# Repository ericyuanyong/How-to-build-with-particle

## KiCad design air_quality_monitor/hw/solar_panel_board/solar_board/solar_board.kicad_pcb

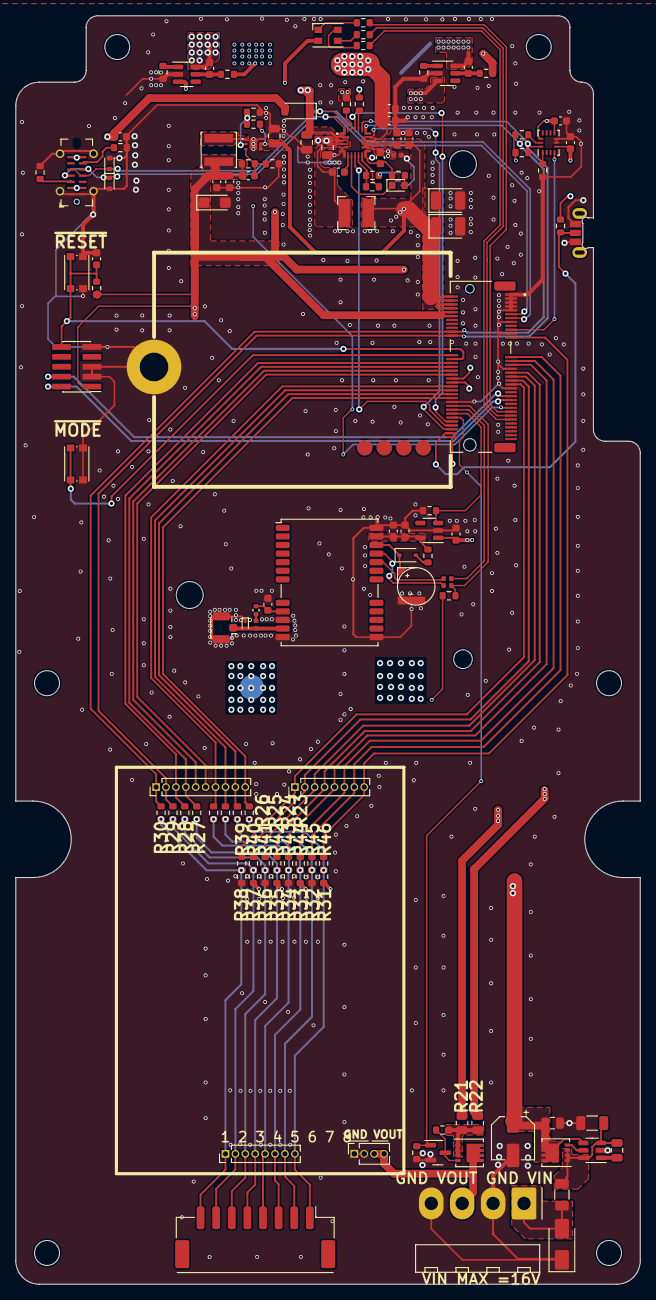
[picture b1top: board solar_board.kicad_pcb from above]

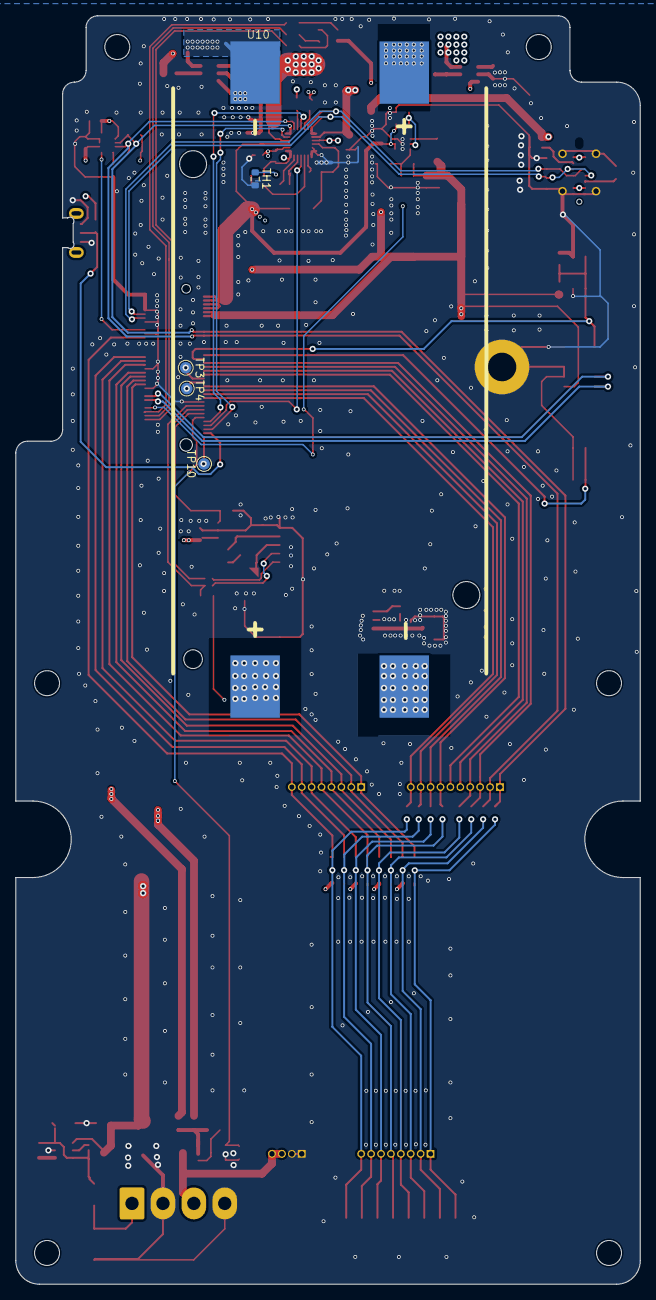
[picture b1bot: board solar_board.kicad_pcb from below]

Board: 4 copper layers, 80.0 x 162.5 mm, 135 parts (5 on the bottom side), 95 nets.

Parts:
@HOLE4, @HOLE5, @HOLE6, @HOLE7, @HOLE8, @HOLE9: (no value)
C1: 2.2uF; C_1206_3216Metric
C2, C10: 10uF; C_0805_2012Metric
C3: 4.7uF; C_0805_2012Metric
C4: 47uF; CP_Elec_5x5.8
C5, C6: 1uF; C_0805_2012Metric
C7: 47nF; C_0603_1608Metric
C8, C24: 10uF; C_0603_1608Metric
C9, C11, C12: 22pF; C_0603_1608Metric
C13, C17, C19, C26: 22uF; C_0603_1608Metric
C14, C15, C16, C18, C20, C21, C23, C25, C27: 0.1uF; C_0603_1608Metric
C22: Super cap; SM3R370301U
C28, C29: 220uF; CP_EIA-3528-12_Kemet-T
C30: 220uF; CP_EIA-3216-10_Kemet-I
D1: LED; LED_0603_1608Metric
D2: LED_RAGB; LED_Cree-PLCC4_3.2x2.8mm_CCW
D3, D4: ESD5Zxx; D_SOD-523
D5: SMAJ28CA; D_SMA
D6: D; D_SOD-323
D7: ESD9B3.3ST5G; D_SOD-923
D8: 1N4448W; D_SOD-123
F1: Fuse; Fuse_1206_3216Metric
FB1, FB2, FB3: L_0402_1005Metric
J1, J8: Conn_01x08; PinHeader_1x08_P1.27mm_Vertical
J2: USB_C_Receptacle_USB2.0_16P; USB_C_Receptacle_G-Switch_GT-USB-7051x
J3: Conn_01x08_Pin; Molex_CLIK-Mate_502443-0870_1x08-1MP_P2.00mm_Vertical
J4: Conn_01x04_Pin; Molex_KK-396_A-41792-0004_1x04_P3.96mm_Horizontal
J5: Conn_Coaxial; U.FL_Hirose_U.FL-R-SMT-1_Vertical
J6: Conn_ARM_JTAG_SWD_10; PinHeader_2x05_P1.27mm_Vertical_SMD
J7: Conn_01x10; PinHeader_1x10_P1.27mm_Vertical
J9: Conn_01x04_Pin; PinSocket_1x04_P1.27mm_Vertical
L1: 2.2uH; L_Changjiang_FNR4020S
L2: 1uH; L_Bourns-SRN4018
L3: 10nH; L_0402_1005Metric
Q1: DMN3008SFG; Diodes_PowerDI3333-8
Q2: DMP3013SFV; Diodes_PowerDI3333-8
Q3: BSS138; SOT-23
R1, R4, R5, R19, R20: 100K; R_0603_1608Metric
R2: DNP; R_0603_1608Metric
R3, R6, R7, R8, R9: TBD; R_0603_1608Metric
R10, R11, R14, R15, R16: 1K; R_0603_1608Metric
R12, R13: 100R; R_0603_1608Metric
R17, R18: 5.1K; R_0603_1608Metric
R21: DNP; R_0805_2012Metric
R22: 0R; R_0805_2012Metric
R23, R24, R25, R26, R27, R28, R29, R30, R31, R32, R33, R34, R35, R36, R37, R38, R39, R40, R41, R42, R43, R44, R45, R46, R47: 0R; R_0603_1608Metric
R48, R49: 470; R_0603_1608Metric
R50, R51: 4.7K; R_0603_1608Metric
R52, R53, R54: 10K; R_0603_1608Metric
R55: 470; R_0402_1005Metric
SW1: ~{MODE}; SW_Push_1P1T_NO_CK_KMR2
SW2: ~{RESET}; SW_Push_1P1T_NO_CK_KMR2
TH1: NTC; R_0603_1608Metric
TP3, TP4, TP10: TestPoint_Pad_D1.5mm
U1: MSoM; Particle_MSOM
U2: MP2733; QFN-26
U3: LM74700; SOT-23-6
U4: TPS62291DRVR; WSON-6-EP
U5, U6: DW06D; SOT-23-6
U7: LDLN025M18R; SOT-23-5
U8: NEO-M8U; ublox_NEO
U9: BMI160; Bosch_LGA-14_3x2.5mm_P0.5mm
U10: KEYSTONE_1134
U11: PTS847MM350LSMTR2LFS

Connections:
+3.3V: C9.1, C11.1, C12.1, C20.1, C21.1, C30.1, D2.2 (A), J6.1 (VTref), L1.2, R4.1, R31.2, R33.2, R35.2, R37.2, R50.2, R51.2, R52.2, R53.2, R54.2, U1.10 (3.3V), U1.12 (3.3V), U9.5 (VDDIO), U9.8 (VDD), U9.12 (CSB)
/power management/VREF: C8.1, R7.2, R8.2, U2.13 (VREF), U2.14 (VREF)
ACCEL_INT: U1.19 (D20), U9.4 (INT1)
D+: D4.1 (K), J2.A6 (D+), J2.B6 (D+), U1.11 (USB_P), U2.1 (USB_DP), U2.26 (USB_DP)
D-: D3.1 (K), J2.A7 (D-), J2.B7 (D-), U1.13 (USB_N), U2.25 (USB_DM)
DCDC_MODE: R1.2, R2.1, U1.59 (D26), U4.2 (MODE)
EXT_A0: J8.8, R46.2, U1.23 (ADC0)
EXT_A1: J8.7, R45.2, U1.33 (ADC1)
EXT_A2: J8.6, R44.2, U1.35 (ADC2)
EXT_A3: J8.5, R43.2, U1.37 (ADC3)
EXT_A4: J8.4, R42.2, U1.41 (ADC4)
EXT_A5: J8.3, R41.2, U1.43 (ADC5)
EXT_A6: J8.2, R40.2, U1.45 (ADC6)
EXT_A7: J8.1, R39.2, U1.47 (ADC7)
EXT_I2C_SCL: J7.1, R30.2, R50.1, U1.20 (SCL), U2.19 (SCL), U2.20 (SCL), U9.13 (SCx)
EXT_I2C_SDA: J7.2, R29.2, R51.1, U1.22 (SDA), U2.21 (SDA), U9.14 (SDx)
EXT_SPI_CS: J7.7, R26.2, U1.48 (CS)
EXT_SPI_MISO: J7.8, R25.2, U1.50 (MISO)
EXT_SPI_MOSI: J7.9, R24.2, U1.52 (MOSI)
EXT_SPI_SCLK: J7.10, R23.2, U1.54 (SCLK)
EXT_UART_CTS: J7.5, U1.40 (CTS)
EXT_UART_RTS: J7.6, U1.42 (RTS)
EXT_UART_RXD: J7.4, R27.2, U1.38 (RXD)
EXT_UART_TXD: J7.3, R28.2, U1.36 (TXD)
GND: C1.2, C3.2, C4.2, C5.2, C6.2, C10.2, C11.2, C12.2, C13.2, C14.2, C17.2, C18.2, C19.2, C20.2, C21.2, C22.2, C23.2, C24.2, C25.2, C26.2, C27.2, C28.2, C29.2, C30.2, D3.2 (A), D4.2 (A), D5.1 (A1), D7.1 (A1), FB3.2, J2.A1 (GND), J2.A12 (GND), J2.B1 (GND), J2.B12 (GND), J2.S1 (SHIELD), J4.2, J4.4, J5.2 (Ext), J6.3 (GND), J6.5 (GND), J6.9 (GNDDetect), J9.1, J9.2, Q3.2 (S), R2.2, R5.2, R10.1, R11.1, R17.1, R18.1, R20.2, R32.2, R34.2, R36.2, R38.2, R47.1, R48.1, SW1.2, SW2.2, TH1.2, U1.1 (GND), U1.3 (GND), U1.5 (GND), U1.7 (GND), U1.9 (GND), U1.15 (GND), U1.21 (GND), U1.39 (GND), U1.49 (GND), U1.56 (GND), U1.80 (GND), U2.5 (PGND), U2.6 (PGND), U2.7 (PGND), U3.2 (GND), U4.6 (GND), U4.7 (PAD), U5.2 (S1), U6.2 (S1), U7.2 (GND), U8.10 (GND), U8.12 (GND), U8.13 (GND), U8.24 (GND), U9.6 (GNDIO), U9.7 (GND), U11.1, U11.3
GNDA: C8.2, FB3.1, R3.2, U2.15 (AGND)
GNSS_PWR_EN: R47.2, U1.62 (D22), U7.3 (EN)
GNSS_RXD: FB2.1, R53.1, U1.58 (D24)
GNSS_TXD: FB1.1, U1.60 (D25)
NEGATIVE_1: C16.1, U6.3 (S2), U6.6 (VSS), U10.2 (NEGATIVE_1)
NEGATIVE_2: C15.1, U5.3 (S2), U5.6 (VSS), U10.4 (NEGATIVE_2)
unnamed: D1.2 (A), R7.1
unnamed: D1.1 (K), U2.9 (STAT)
unnamed: D2.4 (BK), R16.1
unnamed: D2.3 (GK), R15.1
unnamed: D2.1 (RK), R14.1
unnamed: D6.2 (A), R49.1
unnamed: C22.1, D6.1 (K), U8.22 (V_BCKP)
unnamed: D7.2 (A2), J5.1 (In), L3.1, U8.11 (RF_IN)
unnamed: C3.1, C4.1, C5.1, D8.1 (K), Q1.5 (D), U2.2 (VIN), U3.4 (CATHODE)
unnamed: J1.1, J3.8, R30.1, R38.1, R39.1
unnamed: J1.2, J3.7, R29.1, R37.1, R40.1
unnamed: J1.3, J3.6, R28.1, R36.1, R41.1
unnamed: J1.4, J3.5, R27.1, R35.1, R42.1
unnamed: J1.5, J3.4, R26.1, R34.1, R43.1
unnamed: J1.6, J3.3, R25.1, R33.1, R44.1
unnamed: J1.7, J3.2, R24.1, R32.1, R45.1
unnamed: J1.8, J3.1, R23.1, R31.1, R46.1
unnamed: J2.A5 (CC1), R18.2
unnamed: J2.B5 (CC2), R17.2
unnamed: J6.4 (SWCLK/TCK), U1.53 (SWD_CLK)
unnamed: J6.2 (SWDIO/TMS), U1.55 (SWD_DIO)
unnamed: L3.2, R55.1
unnamed: Q1.4 (G), U3.5 (GATE)
unnamed: Q2.4 (G), Q3.3 (D), R19.2
unnamed: Q2.1 (S), Q2.2 (S), Q2.3 (S), R19.1, R21.1, R22.1
unnamed: R9.2, TH1.1
unnamed: SW1.1, U1.32 (~MODE)
unnamed: R54.1, U1.72 (D7), U11.2
unnamed: TP4.1, U1.46 (MODEM_USB_N)
unnamed: TP3.1, U1.44 (MODEM_USB_P)
unnamed: TP10.1, U1.74 (MODEM_VBUS)
unnamed: R16.2, U1.65 (RGB_BLUE)
unnamed: R15.2, U1.63 (RGB_GREEN)
unnamed: R14.2, U1.61 (RGB_RED)
unnamed: C7.1, U2.8 (BST)
unnamed: R8.1, U2.22 (DISC)
unnamed: R3.1, U2.24 (ILIM)
unnamed: R6.1, R9.1, U2.11 (NTC)
unnamed: C7.2, L2.1, U2.4 (SW)
unnamed: R6.2, U2.12 (VNTC)
unnamed: C1.1, C2.1, F1.2, Q1.1 (S), Q1.2 (S), Q1.3 (S), U3.3 (EN), U3.6 (ANODE)
unnamed: C2.2, U3.1 (VCAP)
unnamed: C9.2, R4.2, R5.1, U4.3 (FB)
unnamed: L1.1, U4.1 (SW)
unnamed: R10.2, U5.1 (V-)
unnamed: C15.2, R12.1, U5.5 (VDD)
unnamed: R11.2, U6.1 (V-)
unnamed: C16.2, R13.1, U6.5 (VDD)
unnamed: C18.1, C19.1, R49.2, U7.5 (OUT), U8.23 (VCC)
unnamed: FB2.2, U8.21 (RXD/SPI_MOSI)
unnamed: FB1.2, U8.20 (TXD/SPI_MISO)
unnamed: C23.1, R55.2, U8.9 (VCC_RF)
unnamed: R48.2, U9.1 (SDO)
PMIC_INT: U1.68 (D5), U2.10 (INT)
PMIC_OTG: U1.66 (D4), U2.23 (OTG)
PMID: C10.1, R21.2, U2.3 (PMID)
POSITIVE_1: C26.1, C27.1, R12.2, R13.2, U2.17 (BATT), U10.1 (POSITIVE_1), U10.3 (POSITIVE_2)
PWR_IN: D5.2 (A2), F1.1, J4.1
PWR_OUT: J4.3, J9.3, J9.4, Q2.5 (D)
PWR_VOUT_CTL: Q3.1 (G), R20.1, U1.64 (D23)
VSYS: C6.1, C13.1, C14.1, C17.1, C28.1, C29.1, L2.2, R1.1, R22.2, U1.2 (VCC), U1.4 (VCC), U1.6 (VCC), U1.8 (VCC), U2.16 (SYS), U4.4 (EN), U4.5 (VIN), U7.1 (IN)
VUSB: C24.1, D8.2 (A), J2.A4 (VBUS), J2.A9 (VBUS), J2.B4 (VBUS), J2.B9 (VBUS)
~PMIC_CE: U1.70 (D6), U2.18 (~CE)
~RESET: C25.1, J6.10 (~RESET), R52.1, SW2.1, U1.34 (~RESET)

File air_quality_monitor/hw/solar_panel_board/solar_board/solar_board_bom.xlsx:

Ref | Qnty | Value | Cmp name | Footprint | PN | Purchased QTY
C1 | 1 | 22nF | C_Small | Capacitor_SMD:C_1206_3216Metric |  | 5
C2, C3 | 2 | 0.1uF | C_Small | Capacitor_SMD:C_0805_2012Metric |  | 10
C4 | 1 | 47uF | C_Polarized_US | Capacitor_SMD:CP_Elec_5x5.8 |  | 5
C5 | 1 | 4.7uF | C_Small | Capacitor_SMD:C_0805_2012Metric |  | 5
C6, C10 | 2 | 10uF | C_Small | Capacitor_SMD:C_0805_2012Metric |  | 10
C7 | 1 | 47nF | C_Small | Capacitor_SMD:C_0603_1608Metric |  | 5
C8, C11, C24 | 3 | 10uF | C | Capacitor_SMD:C_0603_1608Metric |  | 15
C9 | 1 | NC | C_Small | Capacitor_SMD:C_0603_1608Metric |  | 5
C12, C14, C15, C16, C18, C20, C21, C23, C25, C27 | 10 | 0.1uF | C_Small | Capacitor_SMD:C_0603_1608Metric |  | 50
C13, C17, C19, C26 | 4 | 22uF | C_Small | Capacitor_SMD:C_0603_1608Metric |  | 20
C22 | 1 | 0.07F | C_Polarized_US | particle_kicad_lib:SM3R370301U |  | 5
C28, C29 | 2 | 220uF | C | Capacitor_Tantalum_SMD:CP_EIA-3528-12_Kemet-T |  | 10
C30 | 1 | 220uF | C | Capacitor_Tantalum_SMD:CP_EIA-3216-10_Kemet-I |  | 5
D1 | 1 | LED | LED | LED_SMD:LED_0603_1608Metric |  | 5
D2 | 1 | LED_RAGB | LED_RAGB | LED_SMD:LED_Cree-PLCC4_3.2x2.8mm_CCW |  | 5
D3, D4 | 2 | ESD5Zxx | ESD5Zxx | Diode_SMD:D_SOD-523 |  | 10
D5 | 1 | SMAJ20CA | SMAJ28CA | Diode_SMD:D_SMA |  | 5
D6 | 1 | 1A/0.4V | D | Diode_SMD:D_SOD-323 |  | 5
D7 | 1 | ESD9B3.3ST5G | ESD9B3.3ST5G | Diode_SMD:D_SOD-923 |  | 5
D8 | 1 | 1N4448W | 1N4448W | Diode_SMD:D_SOD-123 |  | 5
F1 | 1 | 40V/2A | Fuse | Fuse:Fuse_1206_3216Metric |  | 5
FB1, FB2, FB3 | 3 | ~ | FerriteBead_Small | Inductor_SMD:L_0402_1005Metric |  | 15
J1, J8 | 2 | Conn_01x08 | Conn_01x08 | Connector_PinHeader_1.27mm:PinHeader_1x08_P1.27mm_Vertical |  | 10
J2 | 1 | USB_C_Receptacle_USB2.0_16P | USB_C_Receptacle_USB2.0_16P | Connector_USB:USB_C_Receptacle_G-Switch_GT-USB-7051x |  | 5
J3 | 1 | Conn_01x08_Pin | Conn_01x08_Pin | Connector_Molex:Molex_CLIK-Mate_502443-0870_1x08-1MP_P2.00mm_Vertical |  | 5
J4 | 1 | Conn_01x04_Pin | Conn_01x04_Pin | Connector_Molex:Molex_KK-396_A-41792-0004_1x04_P3.96mm_Horizontal |  | 5
J5 | 1 | Conn_Coaxial | Conn_Coaxial | Connector_Coaxial:U.FL_Hirose_U.FL-R-SMT-1_Vertical |  | 5
J6 | 1 | Conn_ARM_JTAG_SWD_10 | Conn_ARM_JTAG_SWD_10 | Connector_PinHeader_1.27mm:PinHeader_2x05_P1.27mm_Vertical_SMD |  | 5
J7 | 1 | Conn_01x10 | Conn_01x10 | Connector_PinHeader_1.27mm:PinHeader_1x10_P1.27mm_Vertical |  | 5
J9 | 1 | Conn_01x04_Pin | Conn_01x04_Pin | Connector_PinSocket_1.27mm:PinSocket_1x04_P1.27mm_Vertical |  | 5
L1 | 1 | 2.2uH | L | Inductor_SMD:L_Changjiang_FNR4020S |  | 5
L2 | 1 | 1uH | L | Inductor_SMD:L_Bourns-SRN4018 |  | 5
L3 | 1 | 10nH | L | Inductor_SMD:L_0402_1005Metric |  | 5
Q1 | 1 | DMN3008SFG | DMN3008SFG | Package_SON:Diodes_PowerDI3333-8 |  | 5
Q2 | 1 | DMP3013SFV | DMP3013SFV | Package_SON:Diodes_PowerDI3333-8 |  | 5
Q3 | 1 | BSS138 | BSS138 | Package_TO_SOT_SMD:SOT-23 |  | 5
R1, R19, R20, R47, R48 | 5 | 100K | R_US | Resistor_SMD:R_0603_1608Metric |  | 25
R2 | 1 | DNP | R_Small | Resistor_SMD:R_0603_1608Metric |  | 5
R3 | 1 | 60R | R_Small | Resistor_SMD:R_0603_1608Metric |  | 5
R4, R23, R24, R25, R26, R27, R28, R29, R30, R31, R32, R33, R34, R35, R36, R37, 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 | 25 | 0R | R_US | Resistor_SMD:R_0603_1608Metric |  | 125
R5 | 1 | NC | R_Small | Resistor_SMD:R_0603_1608Metric |  | 5
R6 | 1 | 11.8K | R_Small | Resistor_SMD:R_0603_1608Metric |  | 5
R7, R8, R52, R53, R54 | 5 | 10K | R_Small | Resistor_SMD:R_0603_1608Metric |  | 25
R9 | 1 | 3.06K | R_Small | Resistor_SMD:R_0603_1608Metric |  | 5
R10, R11, R14, R15, R16 | 5 | 1K | R_Small | Resistor_SMD:R_0603_1608Metric |  | 25
R12, R13, R49 | 3 | 100R | R_US | Resistor_SMD:R_0603_1608Metric |  | 15
R17, R18 | 2 | 5.1K | R_Small | Resistor_SMD:R_0603_1608Metric |  | 10
R21 | 1 | DNP | R_US | Resistor_SMD:R_0805_2012Metric |  | 5
R22 | 1 | 0R | R_US | Resistor_SMD:R_0805_2012Metric |  | 5
R50, R51 | 2 | 4.7K | R_Small | Resistor_SMD:R_0603_1608Metric |  | 10
R55 | 1 | 10R | R_US | Resistor_SMD:R_0402_1005Metric |  | 5
SW1 | 1 | ~{MODE} | SW_MEC_5E | Button_Switch_SMD:SW_Push_1P1T_NO_CK_KMR2 |  | 5
SW2 | 1 | ~{RESET} | SW_MEC_5E | Button_Switch_SMD:SW_Push_1P1T_NO_CK_KMR2 |  | 5
TH1 | 1 | 103AT | Thermistor_NTC | Resistor_SMD:R_0603_1608Metric |  | 5
TP3, TP4, TP10 | 3 | ~ | TestPoint | TestPoint:TestPoint_Pad_D1.5mm |  | 15
U1 | 1 | MSoM | Particle_MSoM | particle_kicad_lib:Particle_MSOM |  | 5
U2 | 1 | MP2733 | MP2733 | particle_kicad_lib:QFN-26 |  | 5
U3 | 1 | LM74700 | LM74700 | Package_TO_SOT_SMD:SOT-23-6 |  | 5
U4 | 1 | TPS62291DRVR | TPS62291DRVR | particle_kicad_lib:WSON-6-EP |  | 5
U5, U6 | 2 | DW06D | DW06D | Package_TO_SOT_SMD:SOT-23-6 |  | 10
U7 | 1 | LDLN025M18R | LDLN025M18R | Package_TO_SOT_SMD:SOT-23-5 |  | 5
U8 | 1 | NEO-M8U | NEO-M8N | RF_GPS:ublox_NEO |  | 5
U9 | 1 | BMI160 | BMI160 | Package_LGA:Bosch_LGA-14_3x2.5mm_P0.5mm |  | 5
U10 | 1 | ~ | LIPO_18650 | particle_kicad_lib:KEYSTONE_1134 |  | 5
U11 | 1 | ~ | TACTEL_SWITCH | particle_kicad_lib:PTS847MM350LSMTR2LFS |  | 5

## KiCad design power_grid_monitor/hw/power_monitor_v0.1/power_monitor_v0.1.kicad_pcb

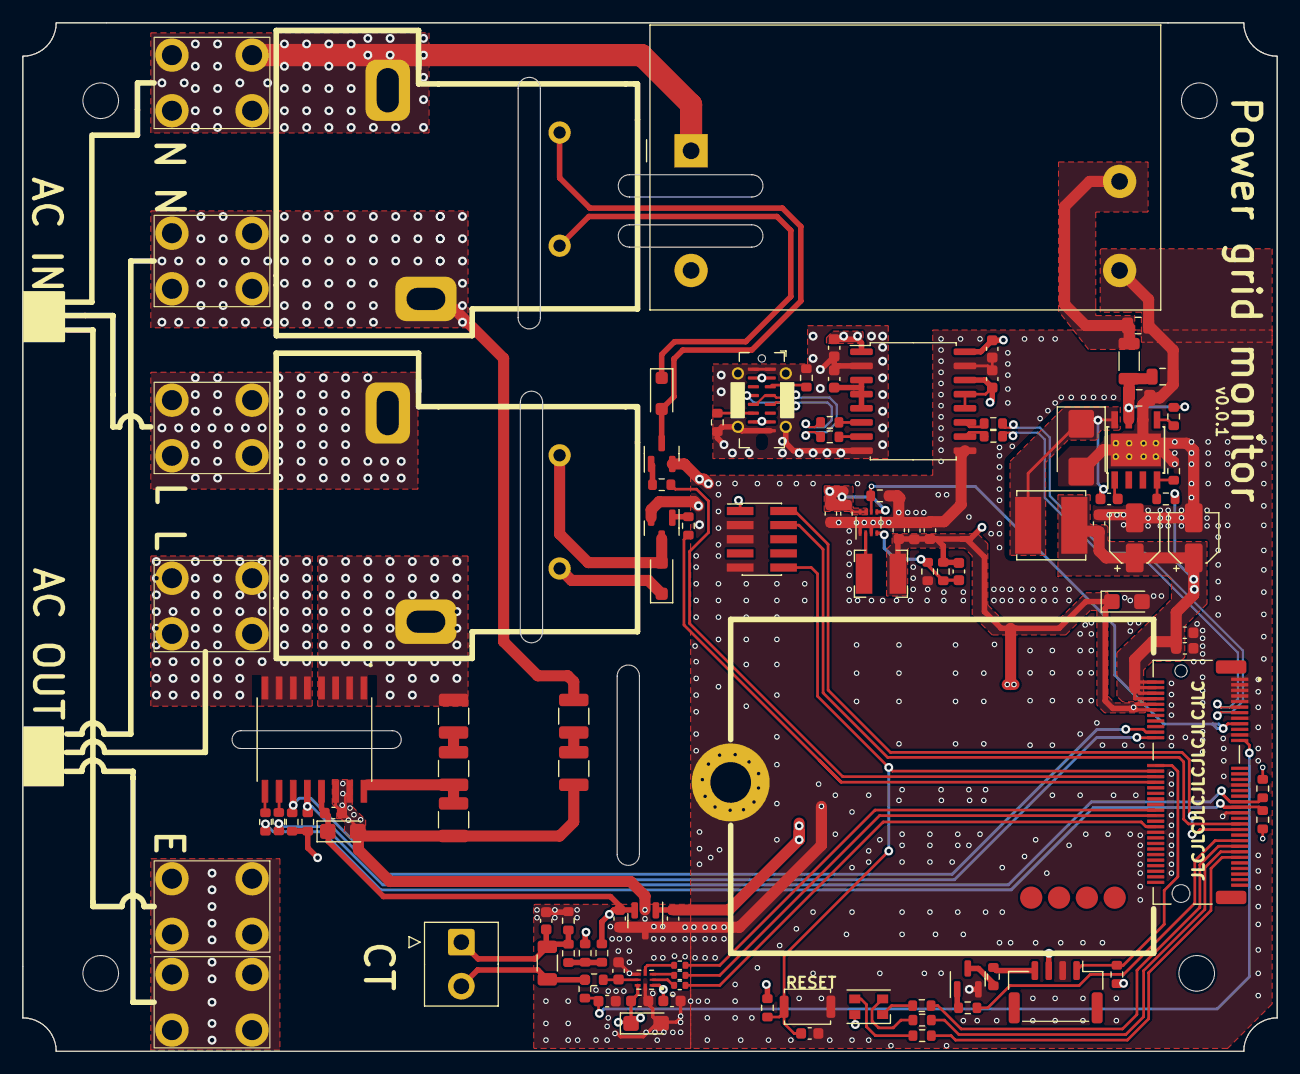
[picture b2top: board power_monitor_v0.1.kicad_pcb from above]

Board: 4 copper layers, 112.7 x 92.4 mm, 105 parts (0 on the bottom side), 72 nets.

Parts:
C1, C2: 0.1uF; C_0805_2012Metric
C3: 22uF; C_0805_2012Metric
C4: 10nF; C_0603_1608Metric
C5, C6: 330uF; CP_Elec_4x5.3
C7, C13, C14, C17, C18, C19, C21, C24, C25, C27, C28, C29, C30: 0.1uF; C_0603_1608Metric
C8: 0.47uF; C_0603_1608Metric
C9: 1uF; C_0603_1608Metric
C10: 8.2pF; C_0603_1608Metric
C11, C12, C15, C26: 10uF; C_0603_1608Metric
C16, C20: 47uF; CP_EIA-3216-12_Kemet-S
C22: 10pF; C_0603_1608Metric
C23: 47uF; CP_EIA-3216-10_Kemet-I
C31: NC; C_0603_1608Metric
D1: B360; D_SMB
D2, D3: 1N4148WS; D_SOD-123F
D4: LED_RAGB; LED_Cree-PLCC4_3.2x2.8mm_CCW
FB1: FerriteBead; L_1206_3216Metric
J1: TE_826576-2_1x02_P3.96mm_Vertical
J2: AC_LIVE_IN; T34001
J3: AC_NEUTRAL_IN; T34001
J4: AC_EARTH_IN; T34001
J5: AC_NEUTRAL_OUT; T34001
J6: AC_LIVE_OUT; T34001
J7: AC_EARTH_OUT; T34001
J8: USB_C_Receptacle_USB2.0_16P; USB_C_Receptacle_G-Switch_GT-USB-7051x
J9: Conn_ARM_JTAG_SWD_10; PinHeader_2x05_P1.27mm_Vertical_SMD
J10: button with LED; JST_GH_BM04B-GHS-TBT_1x04-1MP_P1.25mm_Vertical
K1, K2: Relay_SPST-NO; T9VV1K15-12S
L1: 10uH; L_Bourns_SRN6045TA
L2: 10uH; L_Bourns-SRN4018
PS1: IRM-10-12; Converter_ACDC_MeanWell_IRM-10-xx_THT
Q1, Q2, Q3: BSS138; SOT-23
R1, R14, R40, R41: NC; R_0603_1608Metric
R2: 10K 1%; R_0603_1608Metric
R3: 4.42K 1%; R_0603_1608Metric
R4: 820K 1%; R_0603_1608Metric
R5: 182K 1%; R_0603_1608Metric
R6, R12, R13: 100K; R_0603_1608Metric
R7, R32, R42: 10K; R_0603_1608Metric
R8, R9, R10: 22R; R_0402_1005Metric
R11: 51R; R_1206_3216Metric
R15, R36, R37: 0R; R_0603_1608Metric
R16: 10R; R_0603_1608Metric
R17, R18, R20, R21: 1M; R_1210_3225Metric
R19: TBD; R_1210_3225Metric
R22, R23, R25, R26, R27, R38, R39: 1K; R_0603_1608Metric
R24, R28, R31, R33: 22R; R_0603_1608Metric
R29, R30: 4.7K; R_0603_1608Metric
R34, R35: 5.1K; R_0603_1608Metric
RESET1: SW_Push; SW_Push_SPST_NO_Alps_SKRK
U1: ACS37800; SOIC127P1030X265-16N
U2: ADS7042xDCU; QFN50P150X150X40-8N
U3: REF3033; SOT-23
U4: TPS5430DDA; TI_SO-PowerPAD-8_ThermalVias
U5: TPS62065; WSON-8-1EP_2x2mm_P0.5mm_EP0.9x1.6mm
U6: MSoM; Particle_MSOM
U7: ADUM4160; SOIC-16W_7.5x10.3mm_P1.27mm
U8: ENCLOSURE

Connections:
+3.3VA: C9.2, C16.1, C17.2, C19.2, C20.1, C30.2, R15.1, U1.13 (VCC), U2.1 (DVDD), U2.7 (AVDD), U3.2 (OUT)
+3V3: C10.2, C11.2, C12.2, C13.2, C21.1, C23.1, C26.1, D4.2 (A), J9.1 (VTref), J10.3, L2.2, R4.1, R7.2, R14.1, R29.2, R30.2, R32.2, R40.2, R42.2, U6.10 (3.3V), U6.12 (3.3V), U7.12 (PIN), U7.13 (SPD), U7.14 (VDD2), U7.16 (VBUS2)
+4V: C5.1, C6.1, C7.2, C8.2, C14.2, C15.2, C22.1, C24.1, L1.2, R2.1, U3.1 (IN), U5.5 (EN), U5.7 (AVIN), U5.8 (PVIN), U6.2 (VCC), U6.4 (VCC), U6.6 (VCC), U6.8 (VCC)
+12V: C1.1, D2.1 (K), D3.1 (K), FB1.1, K1.A2, K2.A2, PS1.4 (+Vo)
/MSOM/LED: R38.2, U6.59 (D26)
/MSOM/LED_BLUE: R27.2, U6.65 (RGB_BLUE)
/MSOM/LED_GREEN: R26.2, U6.63 (RGB_GREEN)
/MSOM/LED_RED: R25.2, U6.61 (RGB_RED)
/MSOM/USB_N: R28.2, U6.13 (USB_N)
/MSOM/USB_P: R24.2, U6.11 (USB_P)
/MSOM/U_N: J8.A7 (D-), J8.B7 (D-), R33.1
/MSOM/U_P: J8.A6 (D+), J8.B6 (D+), R31.1
/MSOM/~MODE: J10.1, R40.1, U6.32 (~MODE)
AC_LIVE_IN: J2.1, J2.2, J2.3, J2.4, K1.14, PS1.2 (AC/L)
AC_NEUTRAL_IN: J3.1, J3.2, J3.3, J3.4, K2.14, PS1.1 (AC/N)
AC_NEUTRAL_OUT: J5.1, J5.2, J5.3, J5.4, K2.13, R20.1
AC_SENSOR_LIVE_IN: K1.13, R17.1, U1.1 (IP+), U1.2 (IP+), U1.3 (IP+), U1.4 (IP+)
AC_SENSOR_LIVE_OUT: J6.1, J6.2, J6.3, J6.4, U1.5 (IP-), U1.6 (IP-), U1.7 (IP-), U1.8 (IP-)
CTL_RELAY_LIVE: R22.1, U6.38 (RXD)
CTL_RELAY_NEUTRAL: R23.1, U6.36 (TXD)
CURRENT_ADC: C31.2, R41.2, U6.23 (ADC0)
DCDC_MODE: R6.1, U5.6 (MODE), U6.17 (D21)
DIO_0: R36.1, U1.10 (DIO_0_MOSI)
DIO_1: R37.1, U1.9 (DIO_1/CS)
GNDA: C1.2, C2.2, C3.2, C5.2, C6.2, C7.1, C8.1, C9.1, C11.1, C12.1, C13.1, C14.1, C15.1, C16.2, C17.1, C18.1, C19.1, C20.2, C21.2, C22.2, C23.2, C24.2, C25.2, C26.2, C29.1, C30.1, C31.1, D1.2 (A), J9.3 (GND), J9.5 (GND), J9.9 (GNDDetect), J10.2, PS1.3 (-Vo), Q1.2 (S), Q2.2 (S), Q3.2 (S), R3.2, R5.2, R6.2, R12.2, R19.2, R21.2, RESET1.2, U1.14 (GND), U1.15 (VINN), U2.5 (AINM), U2.8 (GND), U3.3 (GND), U4.6 (GND), U4.9 (GNDPAD), U5.1 (PGND), U5.3 (AGND), U5.9 (PAD), U6.1 (GND), U6.3 (GND), U6.5 (GND), U6.7 (GND), U6.9 (GND), U6.15 (GND), U6.21 (GND), U6.39 (GND), U6.49 (GND), U6.56 (GND), U6.80 (GND), U7.9 (GND2), U7.15 (GND2)
GNDS: C27.2, C28.2, J8.A1 (GND), J8.A12 (GND), J8.B1 (GND), J8.B12 (GND), J8.S1 (SHIELD), R34.1, R35.1, U7.2 (GND1), U7.8 (GND1)
I2C_SCL: R29.1, U1.11 (SCL/SCLK), U6.20 (SCL)
I2C_SDA: R30.1, U1.12 (SDA/MISO), U6.22 (SDA)
unnamed: C4.1, D1.1 (K), L1.1, U4.8 (PH)
unnamed: D2.2 (A), K1.A1, Q1.3 (D)
unnamed: D3.2 (A), K2.A1, Q2.3 (D)
unnamed: D4.4 (BK), R26.1
unnamed: D4.3 (GK), R27.1
unnamed: D4.1 (RK), R25.1
unnamed: C18.2, J1.1, R11.1, R12.1, R13.2
unnamed: J1.2, R11.2, R16.1, R41.1
unnamed: J4.1, J4.2, J4.3, J4.4, J7.1, J7.2, J7.3, J7.4
unnamed: J8.A5 (CC1), R35.2
unnamed: J8.B5 (CC2), R34.2
unnamed: J9.4 (SWCLK/TCK), U6.53 (SWD_CLK)
unnamed: J9.2 (SWDIO/TMS), U6.55 (SWD_DIO)
unnamed: J10.4, R39.1
unnamed: Q1.1 (G), R22.2
unnamed: Q2.1 (G), R23.2
unnamed: Q3.3 (D), R39.2
unnamed: Q3.1 (G), R38.1
unnamed: R13.1, R14.2, R15.2
unnamed: R17.2, R18.1
unnamed: R20.2, R21.1
unnamed: R18.2, R19.1, U1.16 (VINP)
unnamed: C29.2, R16.2, U2.6 (AINP)
unnamed: R9.1, U2.2 (SCLK)
unnamed: R8.1, U2.3 (SDO)
unnamed: R10.1, U2.4 (~CS)
unnamed: C4.2, U4.1 (BOOT)
unnamed: R1.2, U4.5 (EN)
unnamed: C2.1, C3.1, FB1.2, R1.1, U4.7 (VIN)
unnamed: R2.2, R3.1, U4.4 (VSENSE)
unnamed: C10.1, R4.2, R5.1, U5.4 (FB)
unnamed: L2.1, U5.2 (SW)
unnamed: R7.1, R36.2, U6.45 (ADC6)
unnamed: R37.2, R42.1, U6.47 (ADC7)
unnamed: R24.1, U7.10 (DD+)
unnamed: R28.1, U7.11 (DD-)
unnamed: C27.1, U7.3 (VDD1), U7.4 (PDEN), U7.5 (SPU)
unnamed: R31.2, U7.7 (UD+)
unnamed: R33.2, U7.6 (UD-)
unnamed: C28.1, J8.A4 (VBUS), J8.A9 (VBUS), J8.B4 (VBUS), J8.B9 (VBUS), U7.1 (VBUS1)
SPI_MISO: R8.2, U6.50 (MISO)
SPI_SCLK: R9.2, U6.54 (SCLK)
~RESET: C25.1, J9.10 (~RESET), R32.1, RESET1.1, U6.34 (~RESET)
~SPI_CS: R10.2, U6.48 (CS)

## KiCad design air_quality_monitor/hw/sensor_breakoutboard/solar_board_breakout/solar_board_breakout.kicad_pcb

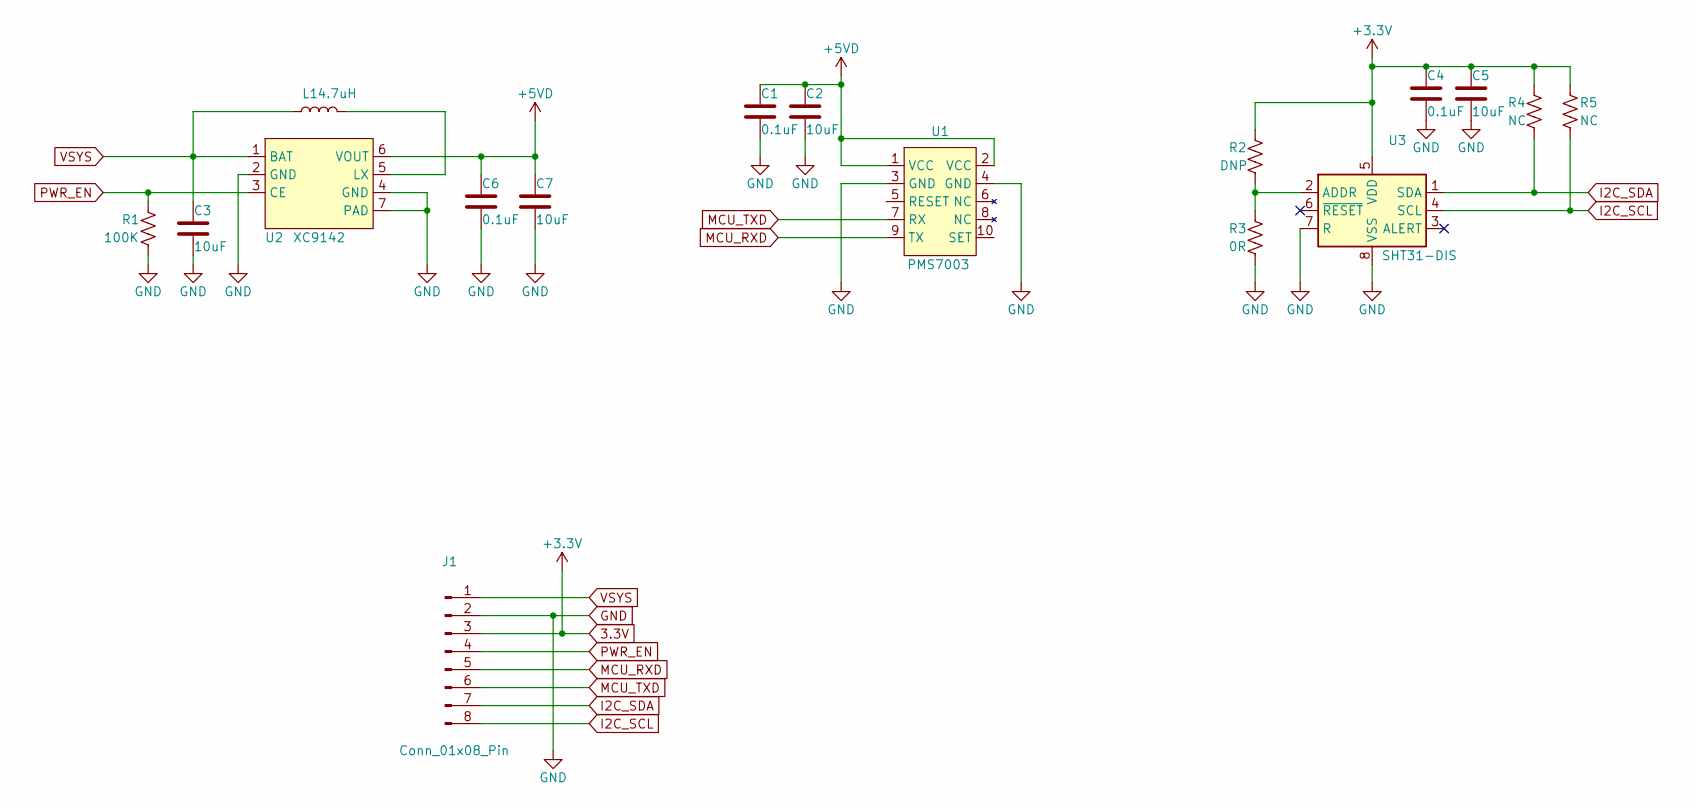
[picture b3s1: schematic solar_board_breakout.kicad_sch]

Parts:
C1, C4, C6: 0.1uF; C_0603_1608Metric
C2, C3, C5, C7: 10uF; C_0603_1608Metric
J1: Conn_01x08_Pin; Molex_CLIK-Mate_502443-0870_1x08-1MP_P2.00mm_Vertical
L1: 4.7uH; L_Abracon_ASPI-3012S
R1: 100K; R_0603_1608Metric
R2: DNP; R_0603_1608Metric
R3: 0R; R_0603_1608Metric
R4, R5: NC; R_0603_1608Metric
U1: PMS7003
U2: XC9142; DFN-6-1EP_1.8X2mm
U3: SHT31-DIS; Sensirion_DFN-8-1EP_2.5x2.5mm_P0.5mm_EP1.1x1.7mm

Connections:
3.3V: C4.1, C5.1, J1.3, R2.1, R4.1, R5.1, U3.5 (VDD)
+5VD: C1.1, C2.1, C6.1, C7.1, U1.1 (VCC), U1.2 (VCC), U2.6 (VOUT)
GND: C1.2, C2.2, C3.2, C4.2, C5.2, C6.2, C7.2, J1.2, R1.2, R3.2, U1.3 (GND), U1.4 (GND), U2.2 (GND), U2.4 (GND), U2.7 (PAD), U3.7 (R), U3.8 (VSS), U3.9 (VSS)
I2C_SCL: J1.8, R5.2, U3.4 (SCL)
I2C_SDA: J1.7, R4.2, U3.1 (SDA)
MCU_RXD: J1.5, U1.9 (TX)
MCU_TXD: J1.6, U1.7 (RX)
unnamed: L1.1, U2.5 (LX)
unnamed: R2.2, R3.1, U3.2 (ADDR)
PWR_EN: J1.4, R1.1, U2.3 (CE)
VSYS: C3.1, J1.1, L1.2, U2.1 (BAT)

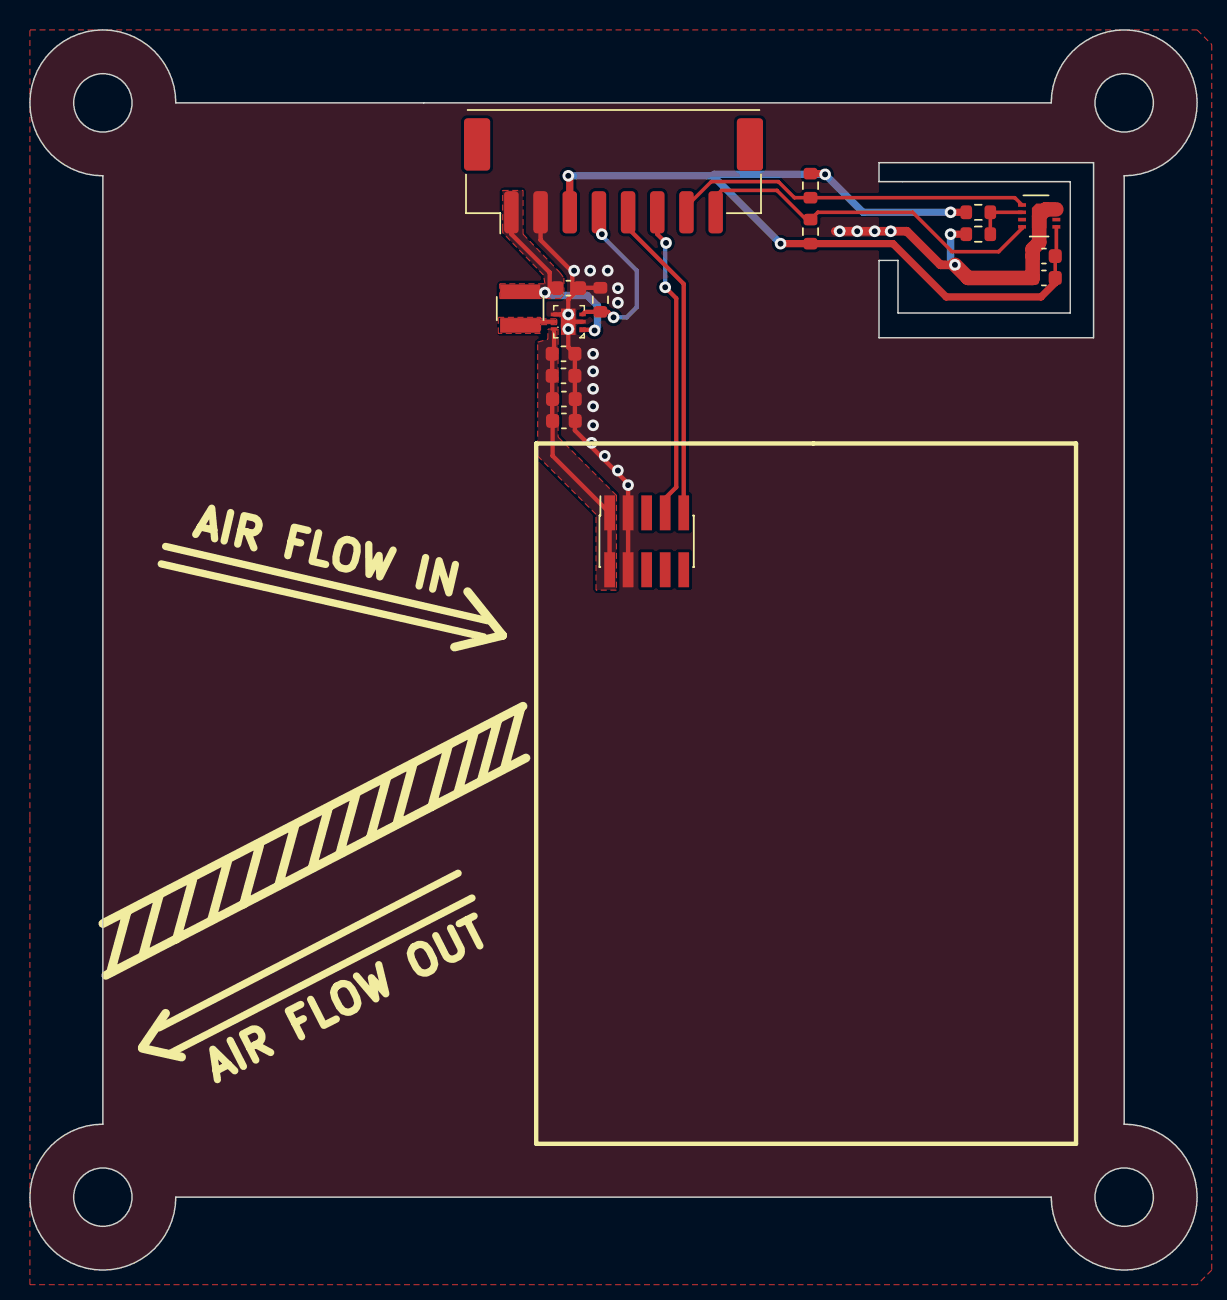
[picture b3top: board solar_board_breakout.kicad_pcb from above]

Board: 2 copper layers, 80.0 x 85.0 mm, 17 parts (0 on the bottom side), 11 nets.

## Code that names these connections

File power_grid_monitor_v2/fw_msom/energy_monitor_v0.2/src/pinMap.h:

#ifndef _PINMAP_H_
#define _PINMAP_H_

#include "Particle.h"


//pin definitions.
#define ADC_CS          D8
#define RELAY_LIVE      RX
#define RELAY_NEUTRAL   TX
#define LED             D26
#define DCDC_MODE       D21
#define BUTTON          A7
#define DIO_0           A5
#define DIO_1           A6



#endif

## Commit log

2024-08-08 add project into this folder
2025-07-11 init comit
2025-07-11 start the project
2025-07-11 add the template that I really want to achieve
2025-07-15 small update
2025-07-16 update the fw
2025-07-21 update the app and database data
2025-07-21 update the port
2025-07-21 update the app
2025-07-22 move the token out of the file
2025-07-28 update the database
2025-07-28 update the msom fw
2025-07-28 update the app without timeout feature in requests function
2025-07-28 update the db
2025-07-28 update the design
2026-03-10 update tomato clock code
